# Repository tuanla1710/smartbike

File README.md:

# Smart Bike Controller V1

Firmware điều khiển xe đạp điện trên ESP32-S3-WROOM-1-N8 (flash 8 MB). Bản thiết kế nằm ở [docs/design/README.md](docs/design/README.md).

Build ảnh firmware chạy trên máy Linux và không cần mạch. Mạch chỉ cần khi nạp và mở console USB.

## Yêu cầu

| Thành phần | Ghi chú |
| --- | --- |
| Linux | Host đã dùng để cài ESP-IDF |
| Python 3 | Lệnh là `python3` |
| GCC | Dùng cho bộ đối chiếu luật điều khiển trên host |
| ESP-IDF v5.5.5 | Nằm ở `sources/esp-idf` |
| CMake và Ninja | ESP-IDF trên Linux không tự tải hai công cụ này |

## Cài ESP-IDF lần đầu

Từ thư mục gốc của repo:

```bash
git clone --depth 1 --branch v5.5.5 --recurse-submodules --shallow-submodules \
  https://github.com/espressif/esp-idf.git sources/esp-idf
cd sources/esp-idf
./install.sh esp32s3
python3 tools/idf_tools.py install cmake ninja
cd ../..
```

`install.sh` tải toolchain Xtensa và Python vào `~/.espressif`. Lệnh `idf_tools.py` tải CMake và Ninja vào cùng chỗ khi máy chưa có hai gói đó.

Mỗi terminal mới phải nạp môi trường trước khi gọi `idf.py`:

```bash
. sources/esp-idf/export.sh
```

Dấu chấm đầu dòng là bắt buộc. Sau khi nạp, `idf.py --version` in `ESP-IDF v5.5.5`.

## Kiểm tra luật điều khiển trên host

Bước này biên dịch lõi C bằng GCC của máy và so với giả lập Python. Chạy trước khi nạp mạch:

```bash
make -C firmware/host
cd firmware
python3 host/diff_oracle.py
python3 -m unittest sim.test_sim
```

Kết quả đúng là `ok files=8 cases=14` và unittest OK. REPL giả lập:

```bash
cd firmware
python3 -m sim
```

## Build firmware

```bash
. sources/esp-idf/export.sh
cd firmware
idf.py set-target esp32s3
idf.py build
```

`set-target` chỉ cần lần đầu, khi chưa có `firmware/sdkconfig`. Các lần sau chỉ cần `idf.py build`.

Ảnh nạp: `firmware/build/smartbike.bin`. Phân vùng ứng dụng là 2 MB (`firmware/partitions_8mb.csv`).

## Nạp và mở console

Cắm cáp USB vào cổng USB của module. Cổng thường là `/dev/ttyACM0`. Kiểm tra bằng `ls /dev/ttyACM*`.

Trong thư mục `firmware/`, shell đã nạp `export.sh`:

```bash
idf.py -p /dev/ttyACM0 flash monitor
```

Dòng đầu console là `ok boot`. Thoát màn hình log bằng Ctrl+].

Nạp lại mà không mở log:

```bash
idf.py -p /dev/ttyACM0 flash
```

Console đi qua USB Serial/JTAG. Lệnh debug nằm ở [docs/design/09-debug-commands.md](docs/design/09-debug-commands.md).

Chạy kịch bản portable trên mạch đã nạp (cần `pyserial`):

```bash
python3 -m pip install -r tools/requirements.txt
python3 -m sim.runner --port /dev/ttyACM0 scenarios/portable/boot.txt
```

Lệnh `hw` và `tick` chỉ có trên giả lập. Trên mạch, `hw` trả `err sim-only`.

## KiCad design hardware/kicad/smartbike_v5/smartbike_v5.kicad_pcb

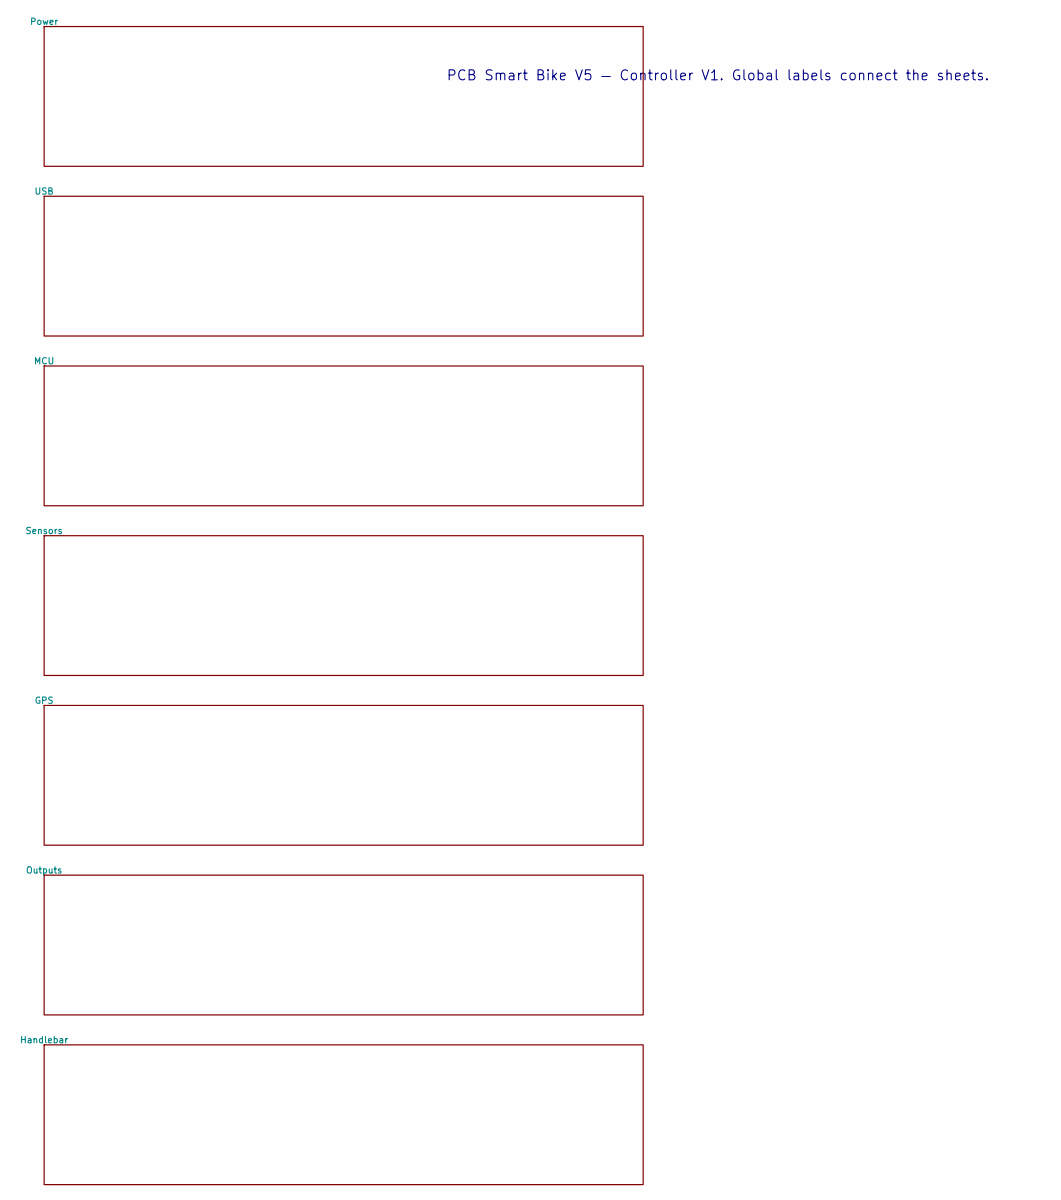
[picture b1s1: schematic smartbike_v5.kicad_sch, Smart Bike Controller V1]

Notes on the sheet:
PCB Smart Bike V5 — Controller V1. Global labels connect the sheets.

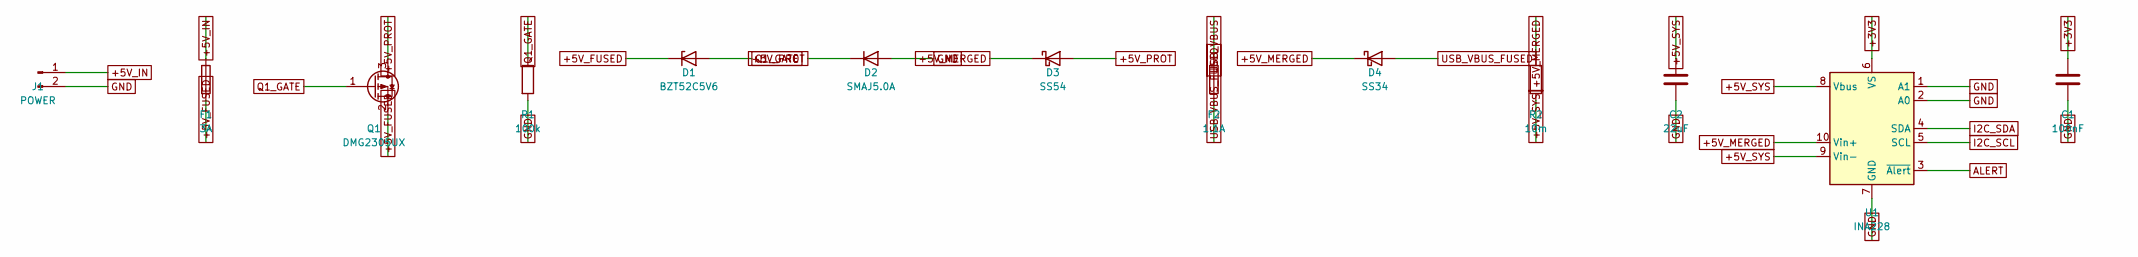
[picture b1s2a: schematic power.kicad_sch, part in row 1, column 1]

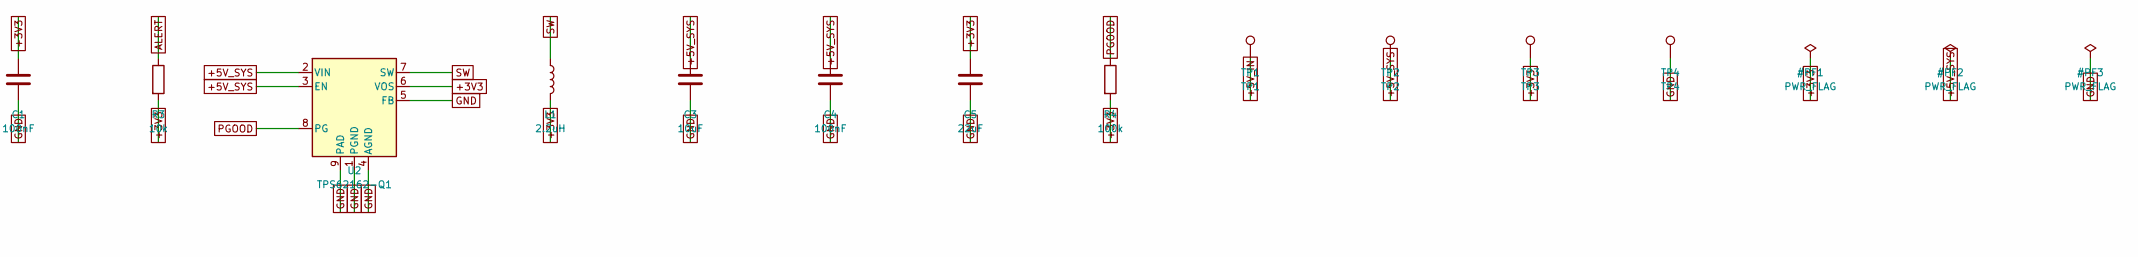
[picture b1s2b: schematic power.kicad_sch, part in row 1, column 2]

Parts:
C1, C4: 100nF; C_0402_1005Metric
C2, C5: 22uF; C_0805_2012Metric
C3: 10uF; C_0805_2012Metric
D1: BZT52C5V6; D_SOD-123
D2: SMAJ5.0A; D_SMA
D3: SS54; D_SMC
D4: SS34; D_SMA
F1: 3A; Fuse_1206_3216Metric
F2: 1.1A; Fuse_1812_4532Metric
J1: POWER; JST_XH_B2B-XH-AM_1x02_P2.50mm_Vertical
L1: 2.2uH; L_1210_3225Metric
Q1: DMG2305UX; SOT-23
R1, R4: 100k; R_0603_1608Metric
R2: 10m; R_2512_6332Metric
R3: 10k; R_0603_1608Metric
TP1: TP1; TestPoint_Pad_D1.5mm
TP2: TP2; TestPoint_Pad_D1.5mm
TP3: TP3; TestPoint_Pad_D1.5mm
TP4: TP4; TestPoint_Pad_D1.5mm
U1: INA228; VSSOP-10_3x3mm_P0.5mm
U2: TPS62162-Q1; WSON-8-1EP_2x2mm_P0.5mm_EP0.9x1.6mm_ThermalVias

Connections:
+5V_FUSED: D1.1 (K), F1.2, Q1.2 (S)
+5V_IN: F1.1, J1.1, TP1.1
+5V_MERGED: D3.1 (K), D4.1 (K), R2.1, U1.10 (Vin+)
+5V_PROT: D2.1 (K), D3.2 (A), Q1.3 (D)
ALERT: R3.1, U1.3 (~Alert)
I2C_SCL: U1.5 (SCL); also elsewhere on the board
I2C_SDA: U1.4 (SDA); also elsewhere on the board
PGOOD: R4.1, U2.8 (PG)
Q1_GATE: D1.2 (A), Q1.1 (G), R1.1
SW: L1.1, U2.7 (SW)
USB_VBUS: F2.1; also elsewhere on the board
USB_VBUS_FUSED: D4.2 (A), F2.2

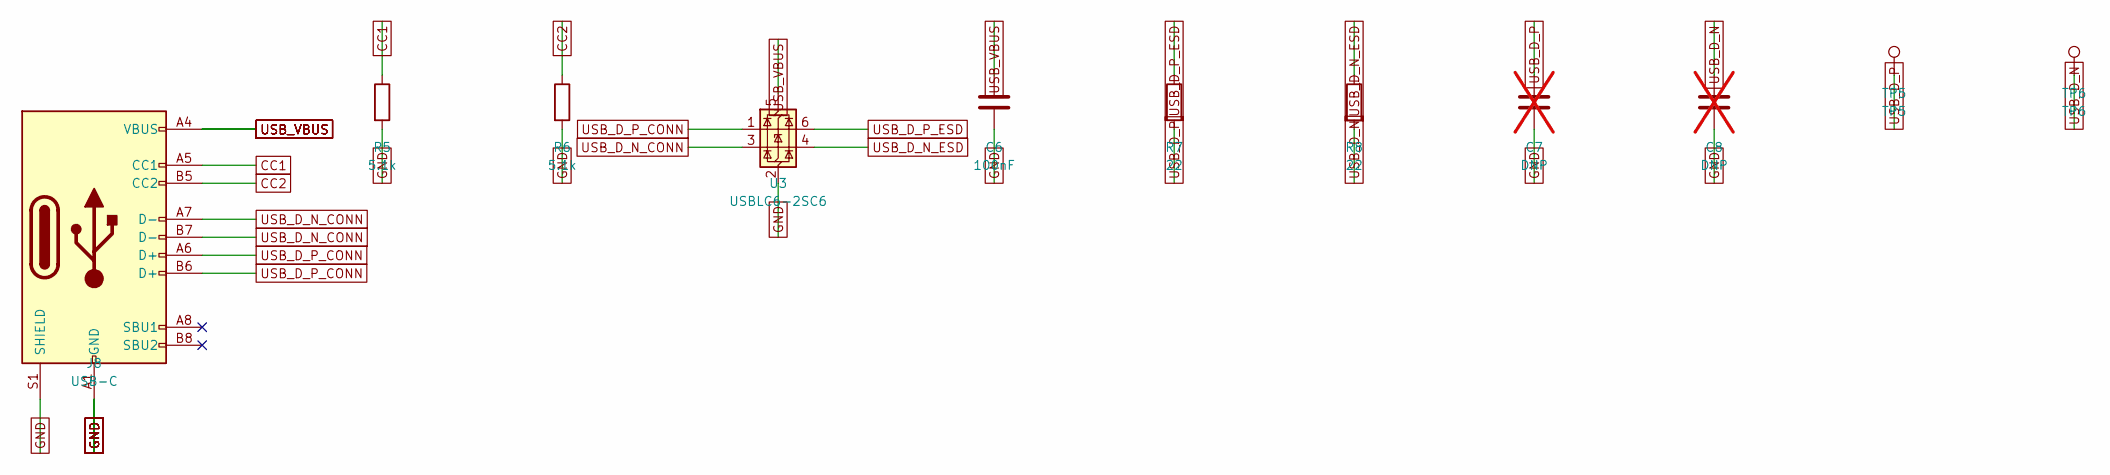
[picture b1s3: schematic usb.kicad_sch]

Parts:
C6: 100nF; C_0402_1005Metric
C7, C8: DNP; C_0402_1005Metric; not fitted
J8: USB-C; USB_C_Receptacle_HCTL_HC-TYPE-C-16P-01A
R5, R6: 5.1k; R_0603_1608Metric
R7, R8: 22; R_0402_1005Metric
TP5: TP5; TestPoint_Pad_D1.5mm
TP6: TP6; TestPoint_Pad_D1.5mm
U3: USBLC6-2SC6; SOT-23-6

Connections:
CC1: J8.A5 (CC1), R5.1
CC2: J8.B5 (CC2), R6.1
USB_D_N: C8.1, R8.2, TP6.1; also elsewhere on the board
USB_D_N_CONN: J8.A7 (D-), J8.B7 (D-), U3.3 (I/O2)
USB_D_N_ESD: R8.1, U3.4 (I/O2)
USB_D_P: C7.1, R7.2, TP5.1; also elsewhere on the board
USB_D_P_CONN: J8.A6 (D+), J8.B6 (D+), U3.1 (I/O1)
USB_D_P_ESD: R7.1, U3.6 (I/O1)
USB_VBUS: C6.1, J8.A4 (VBUS), J8.A9 (VBUS), J8.B4 (VBUS), J8.B9 (VBUS), U3.5 (VBUS); also elsewhere on the board

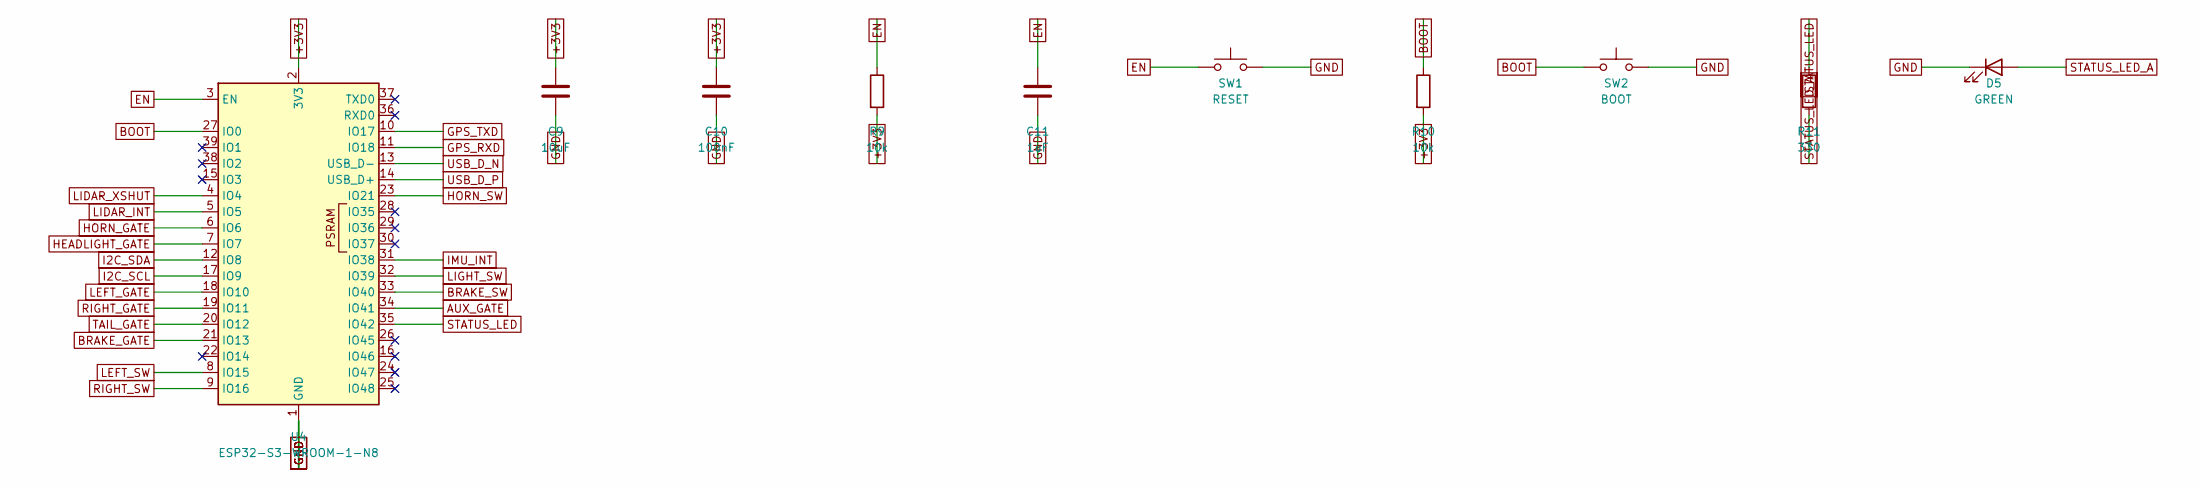
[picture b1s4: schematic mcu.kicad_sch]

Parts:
C9: 10uF; C_0603_1608Metric
C10: 100nF; C_0402_1005Metric
C11: 1uF; C_0402_1005Metric
D5: GREEN; LED_0603_1608Metric
R9, R10: 10k; R_0603_1608Metric
R11: 330; R_0603_1608Metric
SW1: RESET; SW_PUSH_6mm
SW2: BOOT; SW_PUSH_6mm
U4: ESP32-S3-WROOM-1-N8; ESP32-S3-WROOM-1

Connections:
AUX_GATE: U4.34 (IO41); also elsewhere on the board
BOOT: R10.1, SW2.1, U4.27 (IO0)
BRAKE_GATE: U4.21 (IO13); also elsewhere on the board
BRAKE_SW: U4.33 (IO40); also elsewhere on the board
EN: C11.1, R9.1, SW1.1, U4.3 (EN)
GPS_RXD: U4.11 (IO18); also elsewhere on the board
GPS_TXD: U4.10 (IO17); also elsewhere on the board
HEADLIGHT_GATE: U4.7 (IO7); also elsewhere on the board
HORN_GATE: U4.6 (IO6); also elsewhere on the board
HORN_SW: U4.23 (IO21); also elsewhere on the board
I2C_SCL: U4.17 (IO9); also elsewhere on the board
I2C_SDA: U4.12 (IO8); also elsewhere on the board
IMU_INT: U4.31 (IO38); also elsewhere on the board
LEFT_GATE: U4.18 (IO10); also elsewhere on the board
LEFT_SW: U4.8 (IO15); also elsewhere on the board
LIDAR_INT: U4.5 (IO5); also elsewhere on the board
LIDAR_XSHUT: U4.4 (IO4); also elsewhere on the board
LIGHT_SW: U4.32 (IO39); also elsewhere on the board
RIGHT_GATE: U4.19 (IO11); also elsewhere on the board
RIGHT_SW: U4.9 (IO16); also elsewhere on the board
STATUS_LED: R11.1, U4.35 (IO42)
STATUS_LED_A: D5.2 (A), R11.2
TAIL_GATE: U4.20 (IO12); also elsewhere on the board
USB_D_N: U4.13 (USB_D-); also elsewhere on the board
USB_D_P: U4.14 (USB_D+); also elsewhere on the board

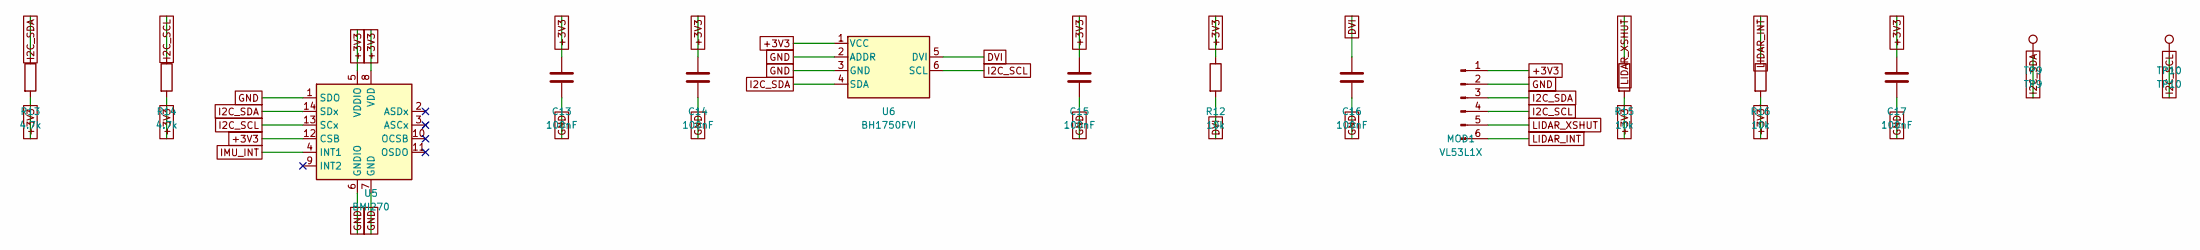
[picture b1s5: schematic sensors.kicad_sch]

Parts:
C13, C14, C15, C16, C17: 100nF; C_0402_1005Metric
MOD1: VL53L1X; JST_XH_B6B-XH-A_1x06_P2.50mm_Vertical
R12, R15, R16: 10k; R_0603_1608Metric
R13, R14: 4.7k; R_0603_1608Metric
TP9: TP9; TestPoint_Pad_D1.5mm
TP10: TP10; TestPoint_Pad_D1.5mm
U5: BMI270; Bosch_LGA-14_3x2.5mm_P0.5mm
U6: BH1750FVI; BH1750FVI_WSOF6

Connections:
DVI: C16.1, R12.2, U6.5 (DVI)
I2C_SCL: MOD1.4, R14.1, TP10.1, U5.13 (SCx), U6.6 (SCL); also elsewhere on the board
I2C_SDA: MOD1.3, R13.1, TP9.1, U5.14 (SDx), U6.4 (SDA); also elsewhere on the board
IMU_INT: U5.4 (INT1); also elsewhere on the board
LIDAR_INT: MOD1.6, R16.1; also elsewhere on the board
LIDAR_XSHUT: MOD1.5, R15.1; also elsewhere on the board

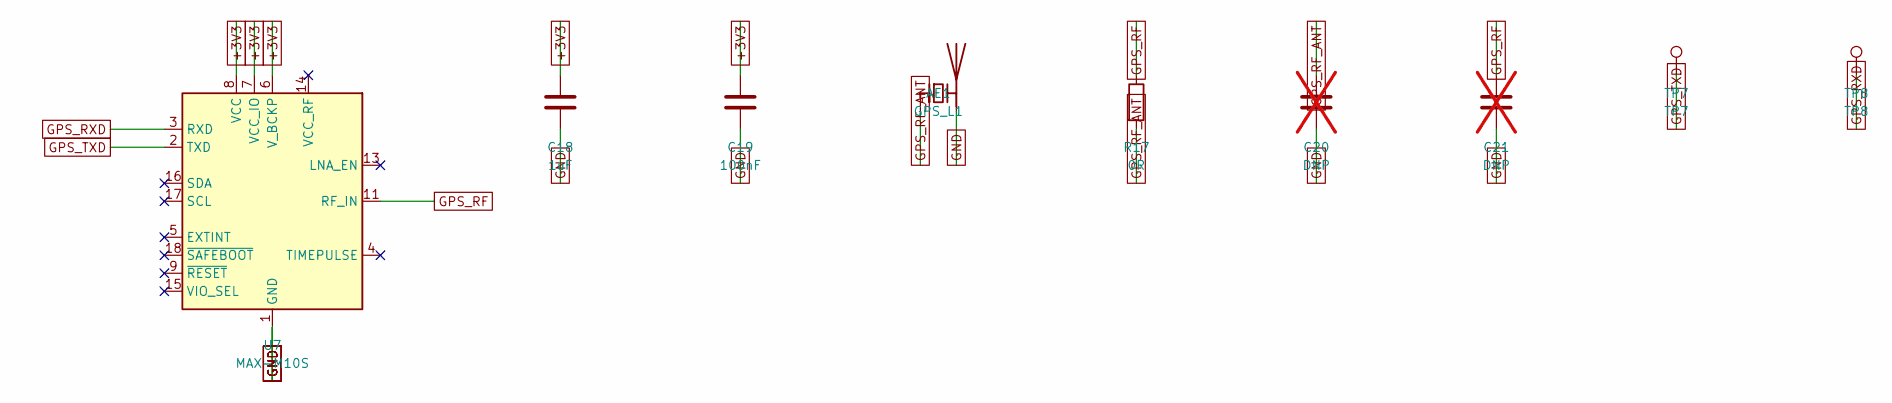
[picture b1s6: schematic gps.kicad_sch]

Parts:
AE1: GPS_L1; Pulse_W3011
C18: 1uF; C_0402_1005Metric
C19: 100nF; C_0402_1005Metric
C20, C21: DNP; C_0402_1005Metric; not fitted
R17: 0R; R_0402_1005Metric
TP7: TP7; TestPoint_Pad_D1.5mm
TP8: TP8; TestPoint_Pad_D1.5mm
U7: MAX-M10S; ublox_MAX

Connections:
GPS_RF: C21.1, R17.1, U7.11 (RF_IN)
GPS_RF_ANT: AE1.1 (FEED), C20.1, R17.2
GPS_RXD: TP8.1, U7.3 (RXD); also elsewhere on the board
GPS_TXD: TP7.1, U7.2 (TXD); also elsewhere on the board

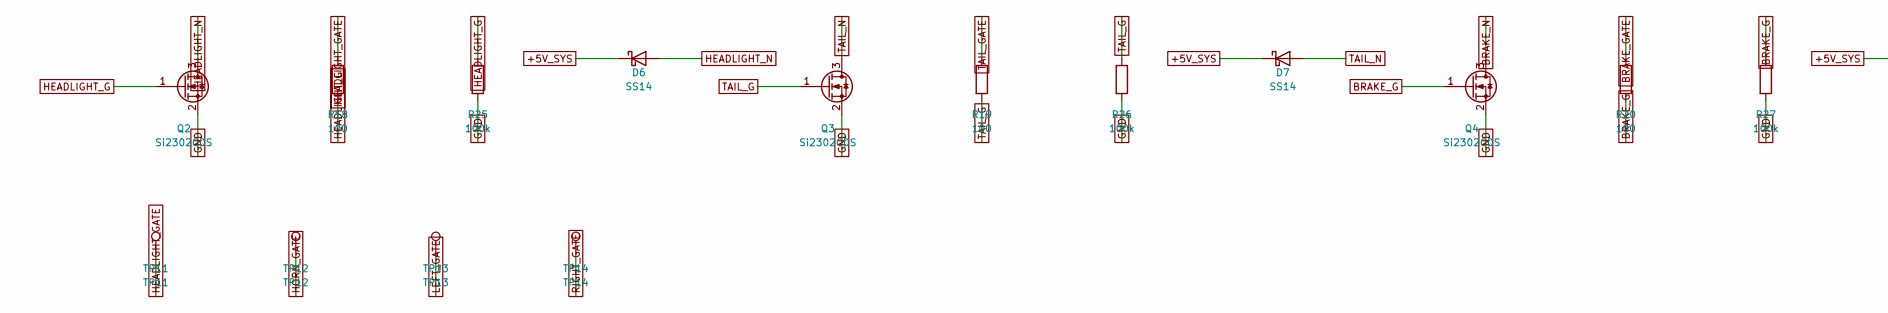
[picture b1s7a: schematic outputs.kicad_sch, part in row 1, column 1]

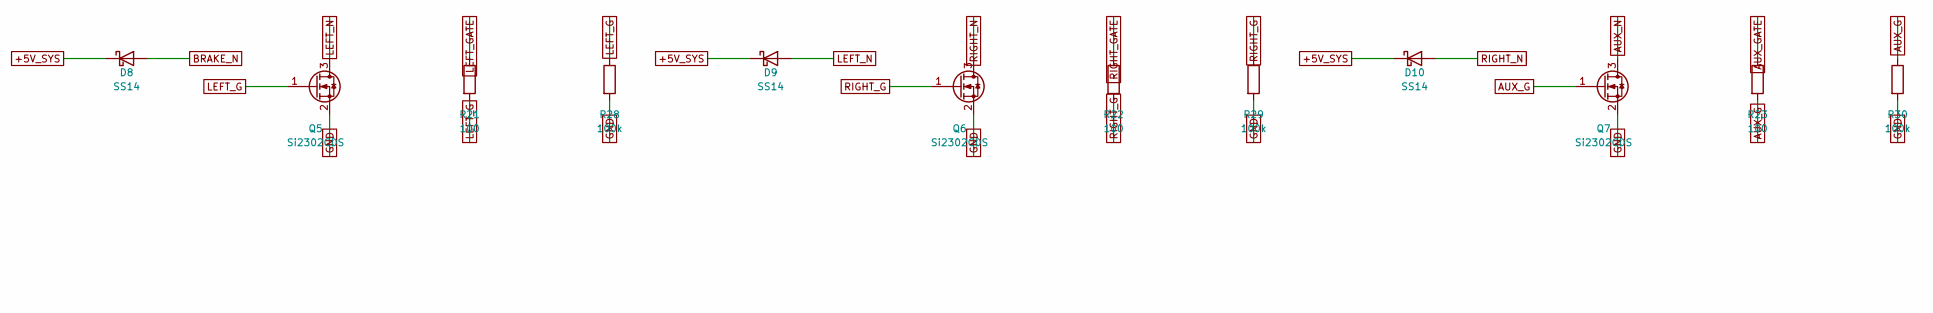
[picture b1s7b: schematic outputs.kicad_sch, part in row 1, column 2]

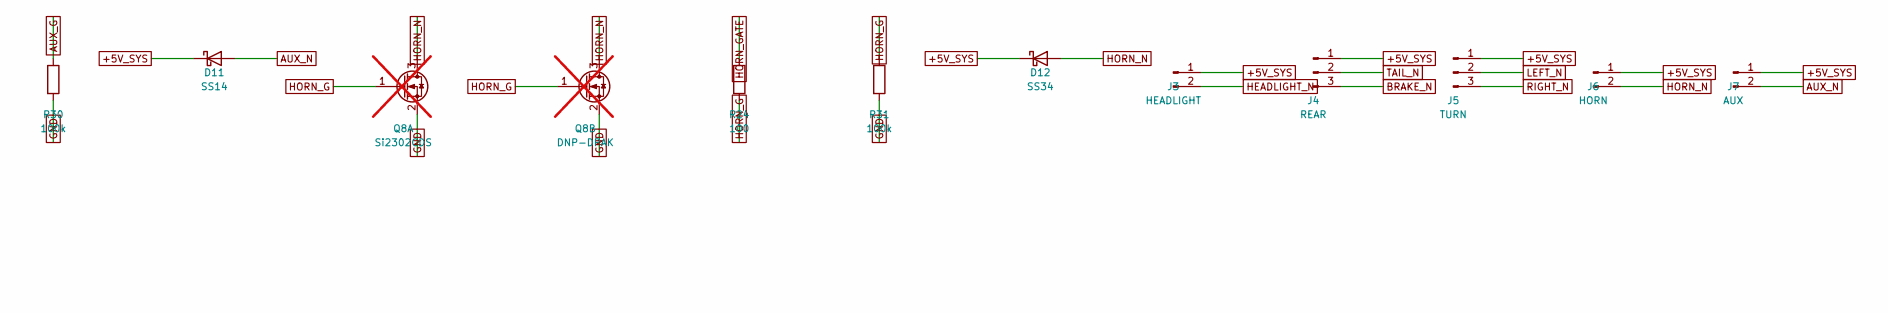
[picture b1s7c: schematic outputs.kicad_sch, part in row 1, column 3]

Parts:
D6, D7, D8, D9, D10, D11: SS14; D_SMA
D12: SS34; D_SMA
J3: HEADLIGHT; JST_XH_B2B-XH-AM_1x02_P2.50mm_Vertical
J4: REAR; JST_XH_B3B-XH-A_1x03_P2.50mm_Vertical
J5: TURN; JST_XH_B3B-XH-A_1x03_P2.50mm_Vertical
J6: HORN; JST_XH_B2B-XH-AM_1x02_P2.50mm_Vertical
J7: AUX; JST_XH_B2B-XH-AM_1x02_P2.50mm_Vertical
Q2, Q3, Q4, Q5, Q6, Q7: Si2302CDS; SOT-23
Q8A: Si2302CDS; SOT-23; not fitted
Q8B: DNP-DPAK; TO-252-2_GSD; not fitted
R18, R19, R20, R21, R22, R23, R24: 100; R_0603_1608Metric
R25, R26, R27, R28, R29, R30, R31: 100k; R_0603_1608Metric
TP11: TP11; TestPoint_Pad_D1.5mm
TP12: TP12; TestPoint_Pad_D1.5mm
TP13: TP13; TestPoint_Pad_D1.5mm
TP14: TP14; TestPoint_Pad_D1.5mm

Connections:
AUX_G: Q7.1 (G), R23.2, R30.1
AUX_GATE: R23.1; also elsewhere on the board
AUX_N: D11.2 (A), J7.2, Q7.3 (D)
BRAKE_G: Q4.1 (G), R20.2, R27.1
BRAKE_GATE: R20.1; also elsewhere on the board
BRAKE_N: D8.2 (A), J4.3, Q4.3 (D)
HEADLIGHT_G: Q2.1 (G), R18.2, R25.1
HEADLIGHT_GATE: R18.1, TP11.1; also elsewhere on the board
HEADLIGHT_N: D6.2 (A), J3.2, Q2.3 (D)
HORN_G: Q8A.1 (G), Q8B.1 (G), R24.2, R31.1
HORN_GATE: R24.1, TP12.1; also elsewhere on the board
HORN_N: D12.2 (A), J6.2, Q8A.3 (D), Q8B.3 (D)
LEFT_G: Q5.1 (G), R21.2, R28.1
LEFT_GATE: R21.1, TP13.1; also elsewhere on the board
LEFT_N: D9.2 (A), J5.2, Q5.3 (D)
RIGHT_G: Q6.1 (G), R22.2, R29.1
RIGHT_GATE: R22.1, TP14.1; also elsewhere on the board
RIGHT_N: D10.2 (A), J5.3, Q6.3 (D)
TAIL_G: Q3.1 (G), R19.2, R26.1
TAIL_GATE: R19.1; also elsewhere on the board
TAIL_N: D7.2 (A), J4.2, Q3.3 (D)

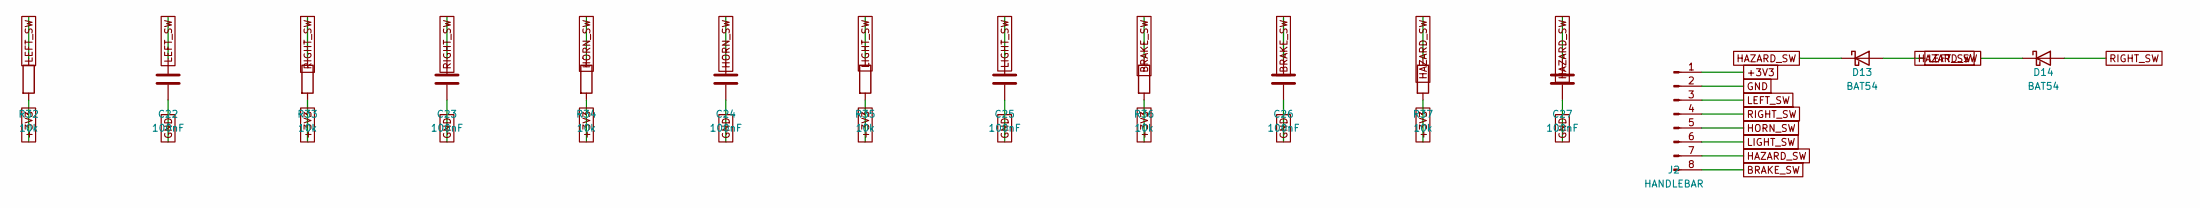
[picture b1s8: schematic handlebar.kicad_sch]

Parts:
C22, C23, C24, C25, C26, C27: 100nF; C_0402_1005Metric
D13, D14: BAT54; D_SOD-123
J2: HANDLEBAR; JST_XH_B8B-XH-A_1x08_P2.50mm_Vertical
R32, R33, R34, R35, R36, R37: 10k; R_0603_1608Metric

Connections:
BRAKE_SW: C26.1, J2.8, R36.1; also elsewhere on the board
HAZARD_SW: C27.1, D13.1 (K), D14.1 (K), J2.7, R37.1
HORN_SW: C24.1, J2.5, R34.1; also elsewhere on the board
LEFT_SW: C22.1, D13.2 (A), J2.3, R32.1; also elsewhere on the board
LIGHT_SW: C25.1, J2.6, R35.1; also elsewhere on the board
RIGHT_SW: C23.1, D14.2 (A), J2.4, R33.1; also elsewhere on the board

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
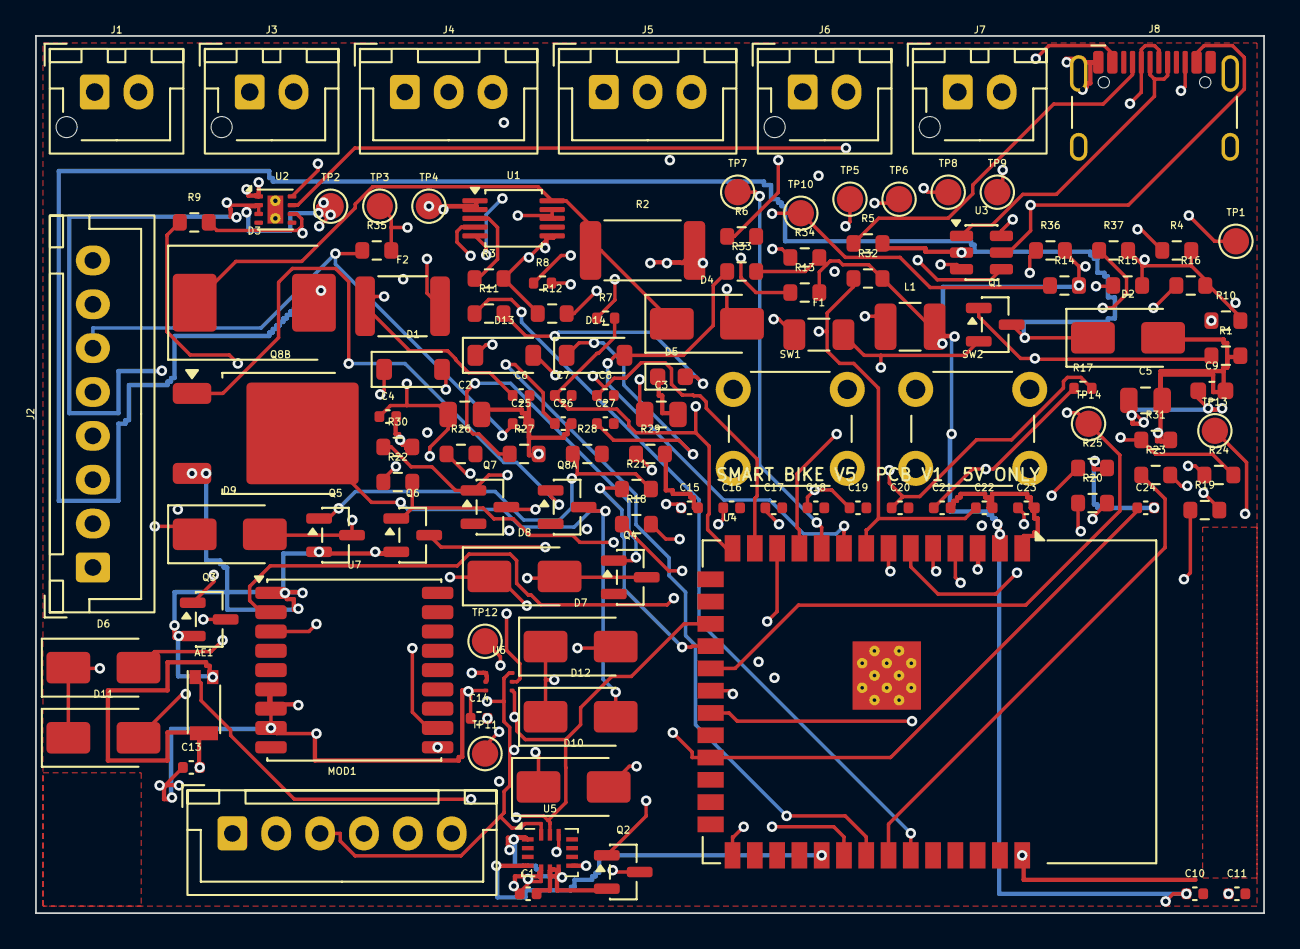
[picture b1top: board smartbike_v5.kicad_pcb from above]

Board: 4 copper layers, 70.0 x 50.0 mm, 122 parts (0 on the bottom side), 62 nets.

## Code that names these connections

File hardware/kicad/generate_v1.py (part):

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        R("R12", "10k", R0603, "+3V3", "DVI", "sensors", "sensors"),
        C("C16", "100nF", C0402, "DVI", "GND", "sensors", "sensors"),
        Part("MOD1", "Connector:Conn_01x06_Pin", "VL53L1X", "Connector_JST:JST_XH_B6B-XH-A_1x06_P2.50mm_Vertical", {
            "Pin_1": "+3V3", "Pin_2": "GND", "Pin_3": "I2C_SDA", "Pin_4": "I2C_SCL",
            "Pin_5": "LIDAR_XSHUT", "Pin_6": "LIDAR_INT",
        }, "sensors", "lidar"),
        R("R15", "10k", R0603, "LIDAR_XSHUT", "+3V3", "sensors", "sensors"),
        R("R16", "10k", R0603, "LIDAR_INT", "+3V3", "sensors", "sensors"),
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    # only if we insert the resistor. Reconnect AE1 feed to the antenna side.
    for part in p:
        if part.ref == "AE1":
            part.pinmap["FEED"] = "GPS_RF_ANT"
    # Outputs
    channels = [
        ("Q2", "Si2302CDS", "HEADLIGHT_GATE", "HEADLIGHT_N", "R18", "R25", "D6", "SS14", DSMA),
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        R("R31", "100k", R0603, "HORN_G", "GND", "outputs", "fet"),
        diode("D12", "SS34", DSMA, "+5V_SYS", "HORN_N", "outputs", "fet"),
        Part("J3", "Connector:Conn_01x02_Pin", "HEADLIGHT", "Connector_JST:JST_XH_B2B-XH-AM_1x02_P2.50mm_Vertical",
             {"Pin_1": "+5V_SYS", "Pin_2": "HEADLIGHT_N"}, "outputs", "conn"),
        Part("J4", "Connector:Conn_01x03_Pin", "REAR", "Connector_JST:JST_XH_B3B-XH-A_1x03_P2.50mm_Vertical",
             {"Pin_1": "+5V_SYS", "Pin_2": "TAIL_N", "Pin_3": "BRAKE_N"}, "outputs", "conn"),
        Part("J5", "Connector:Conn_01x03_Pin", "TURN", "Connector_JST:JST_XH_B3B-XH-A_1x03_P2.50mm_Vertical",
             {"Pin_1": "+5V_SYS", "Pin_2": "LEFT_N", "Pin_3": "RIGHT_N"}, "outputs", "conn"),
        Part("J6", "Connector:Conn_01x02_Pin", "HORN", "Connector_JST:JST_XH_B2B-XH-AM_1x02_P2.50mm_Vertical",
             {"Pin_1": "+5V_SYS", "Pin_2": "HORN_N"}, "outputs", "conn"),
        Part("J7", "Connector:Conn_01x02_Pin", "AUX", "Connector_JST:JST_XH_B2B-XH-AM_1x02_P2.50mm_Vertical",
             {"Pin_1": "+5V_SYS", "Pin_2": "AUX_N"}, "outputs", "conn"),
    ]
    # Handlebar
    switches = [
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        p.append(C(cc, "100nF", C0402, net, "GND", "handlebar", "logic"))
    p += [
        Part("J2", "Connector:Conn_01x08_Pin", "HANDLEBAR", "Connector_JST:JST_XH_B8B-XH-A_1x08_P2.50mm_Vertical", {
            "Pin_1": "+3V3", "Pin_2": "GND", "Pin_3": "LEFT_SW", "Pin_4": "RIGHT_SW",
            "Pin_5": "HORN_SW", "Pin_6": "LIGHT_SW", "Pin_7": "HAZARD_SW", "Pin_8": "BRAKE_SW",
        }, "handlebar", "conn"),
        diode("D13", "BAT54", DSOD, "HAZARD_SW", "LEFT_SW", "handlebar", "logic"),
        diode("D14", "BAT54", DSOD, "HAZARD_SW", "RIGHT_SW", "handlebar", "logic"),
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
